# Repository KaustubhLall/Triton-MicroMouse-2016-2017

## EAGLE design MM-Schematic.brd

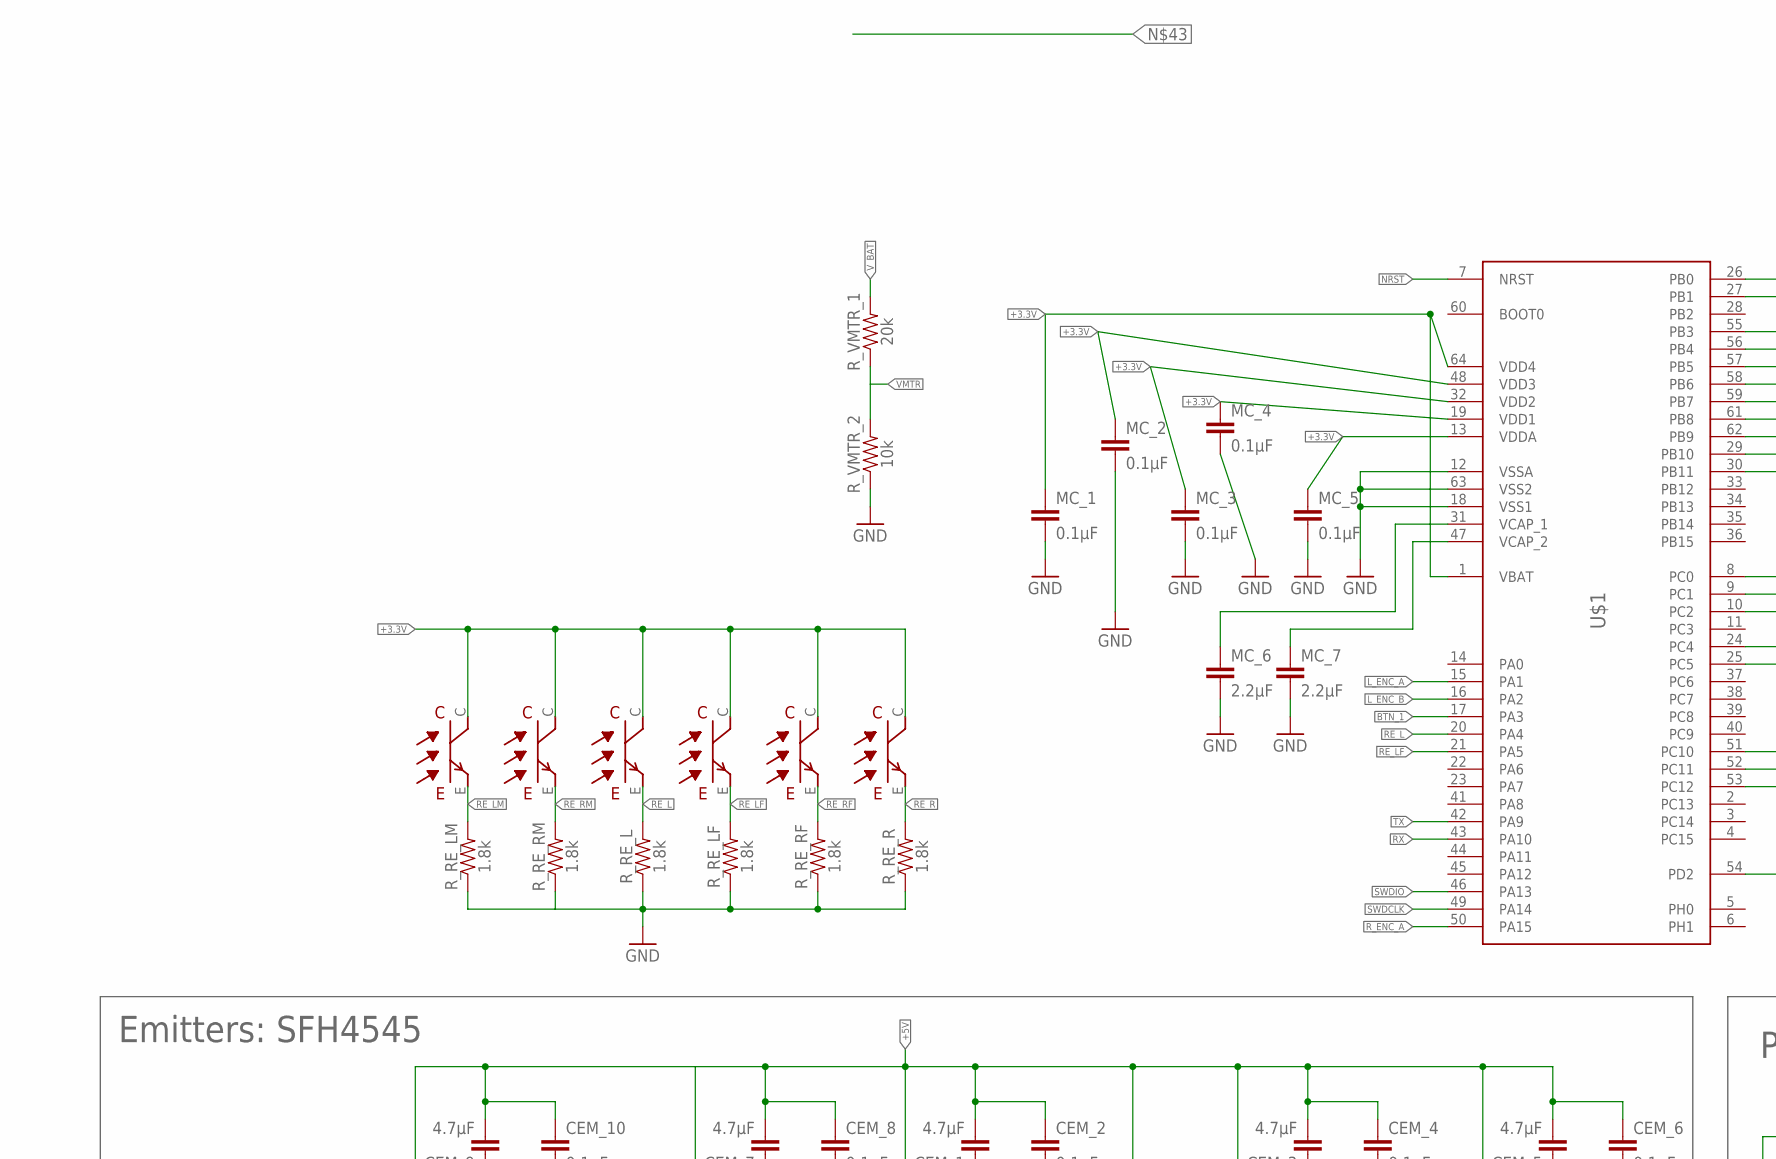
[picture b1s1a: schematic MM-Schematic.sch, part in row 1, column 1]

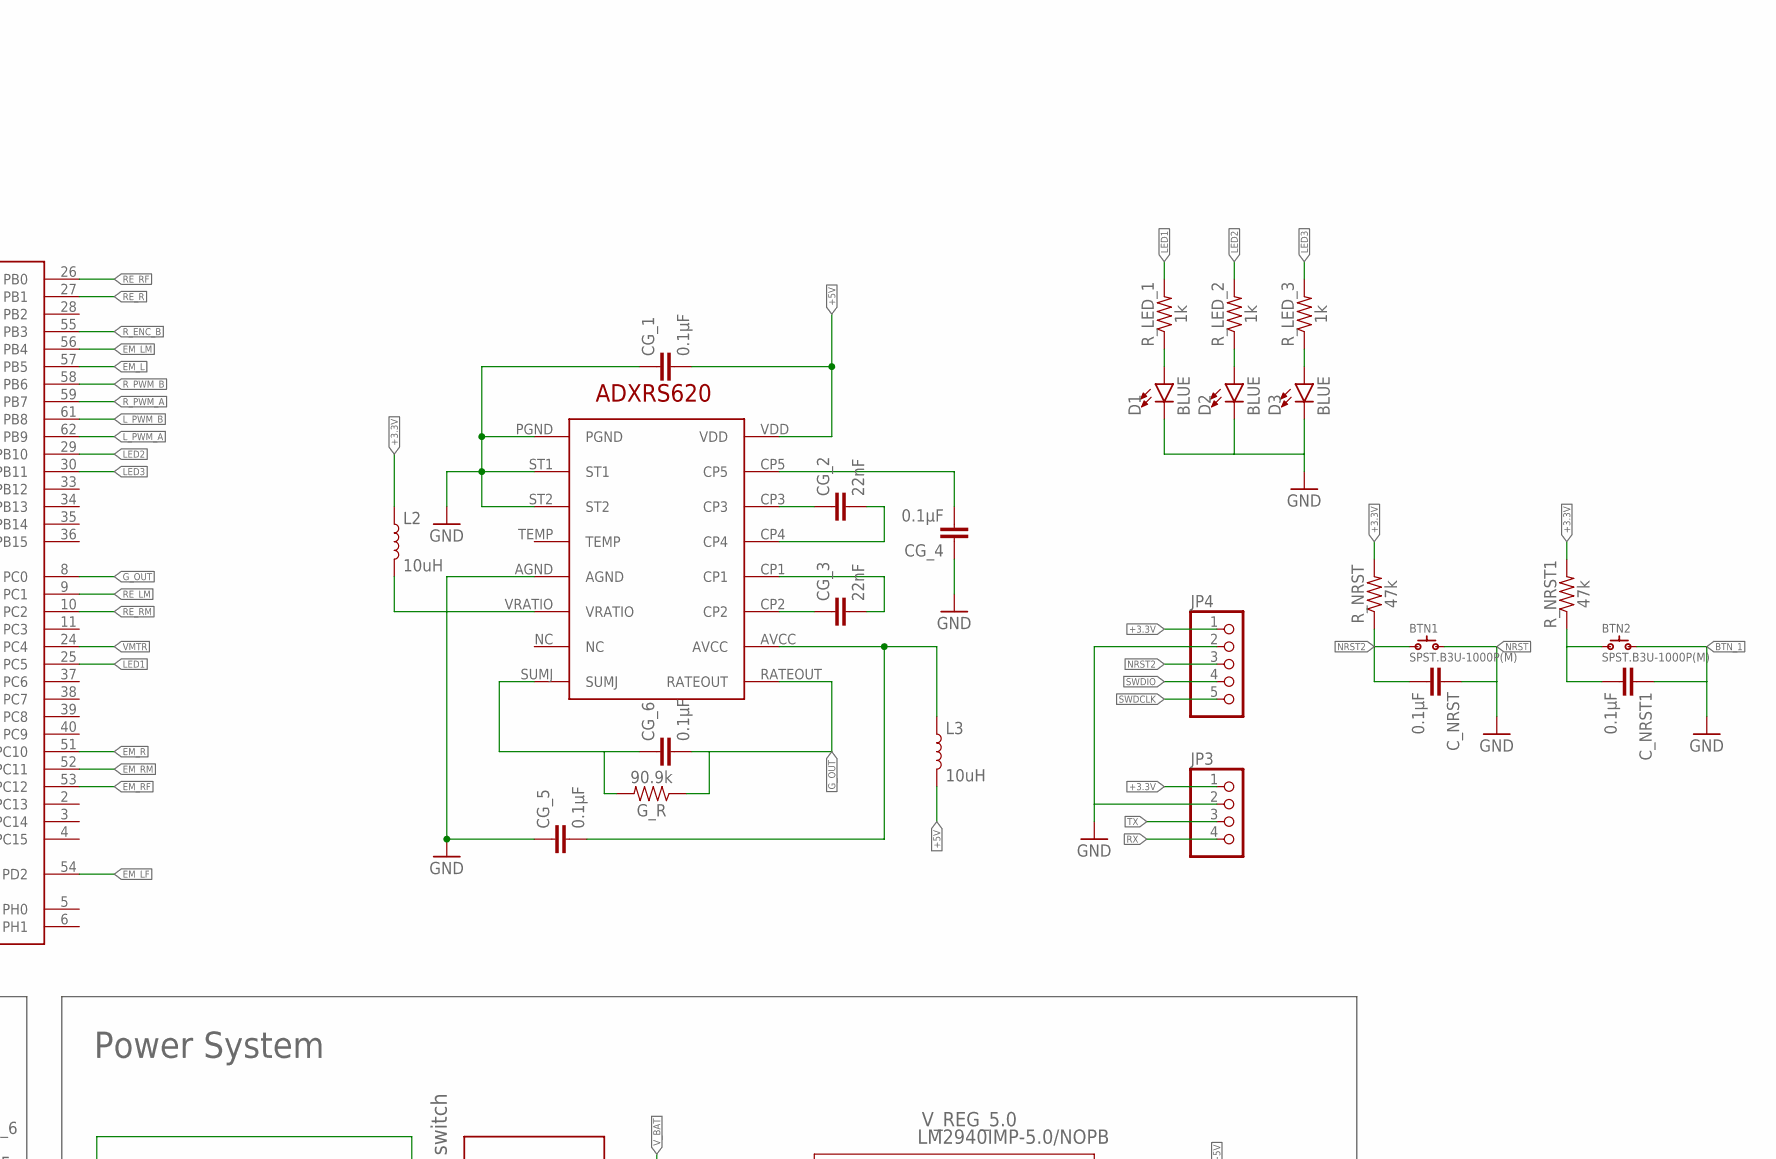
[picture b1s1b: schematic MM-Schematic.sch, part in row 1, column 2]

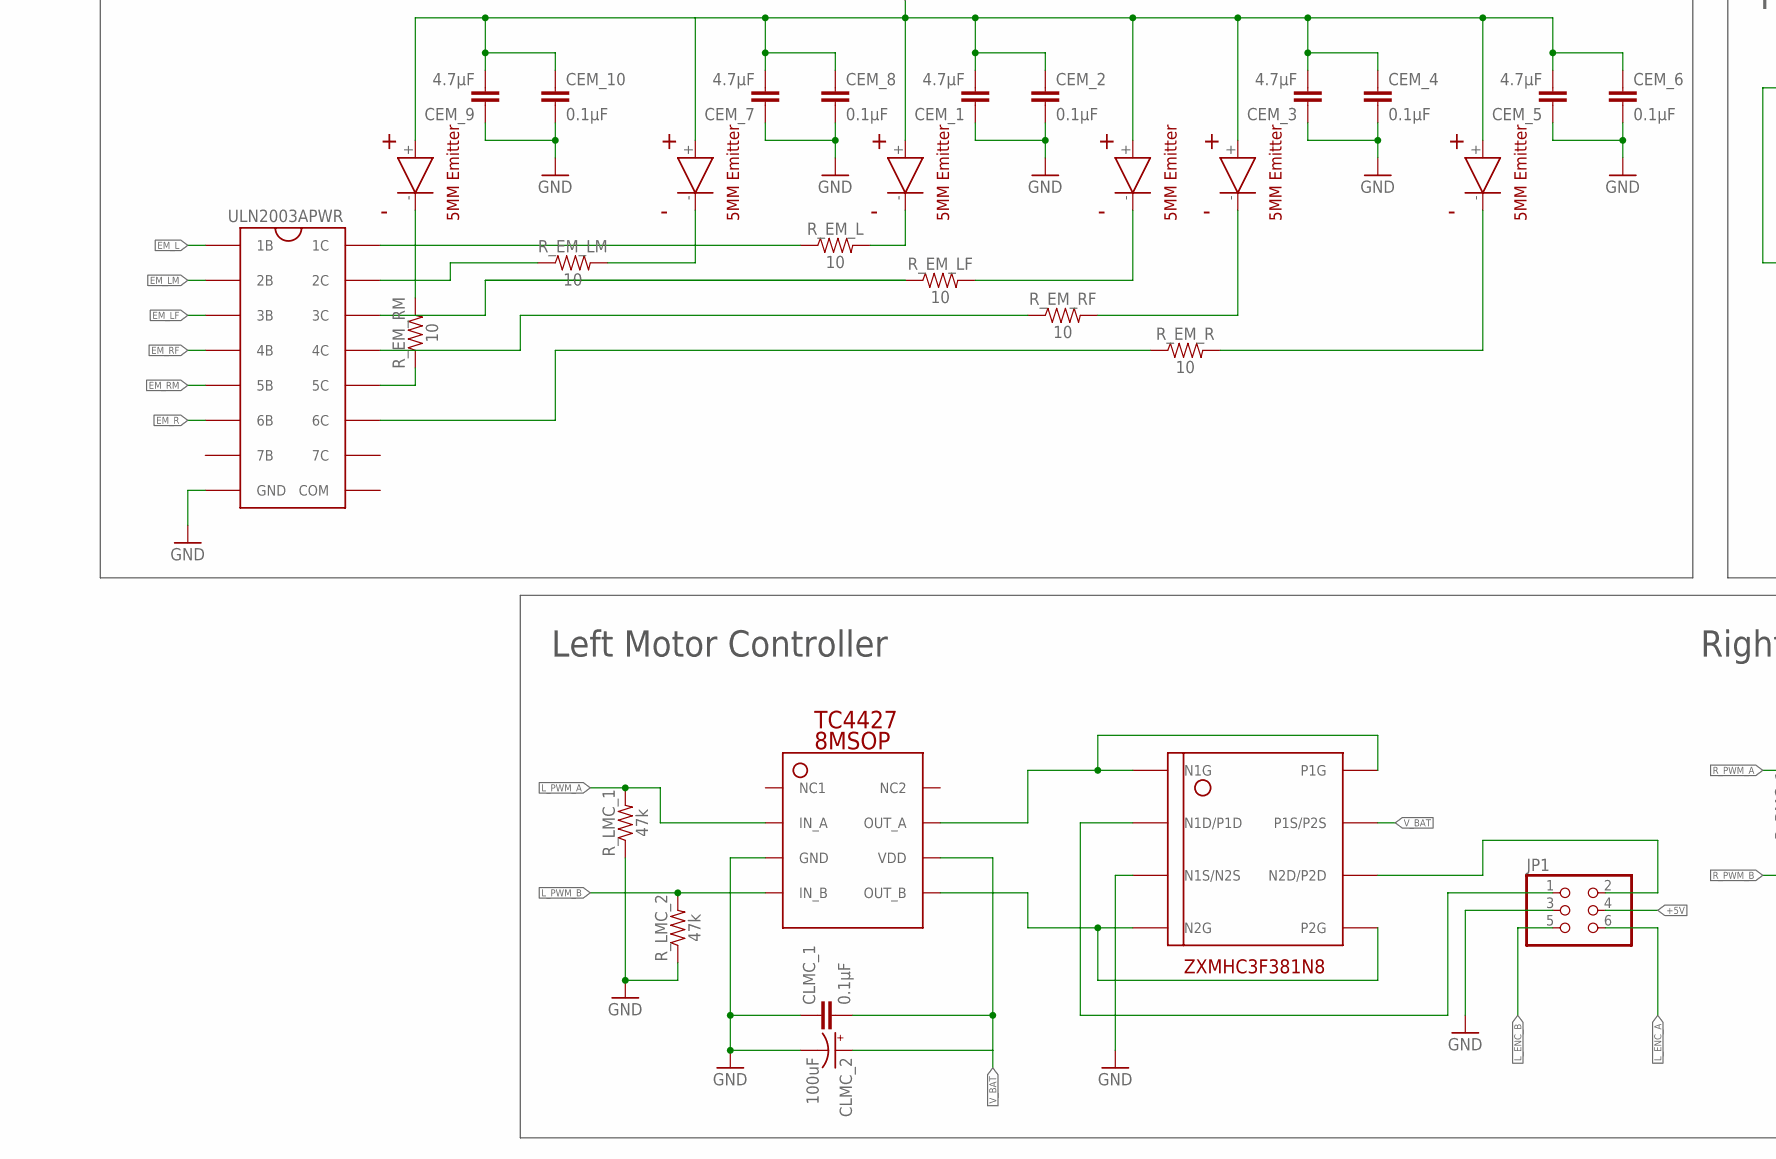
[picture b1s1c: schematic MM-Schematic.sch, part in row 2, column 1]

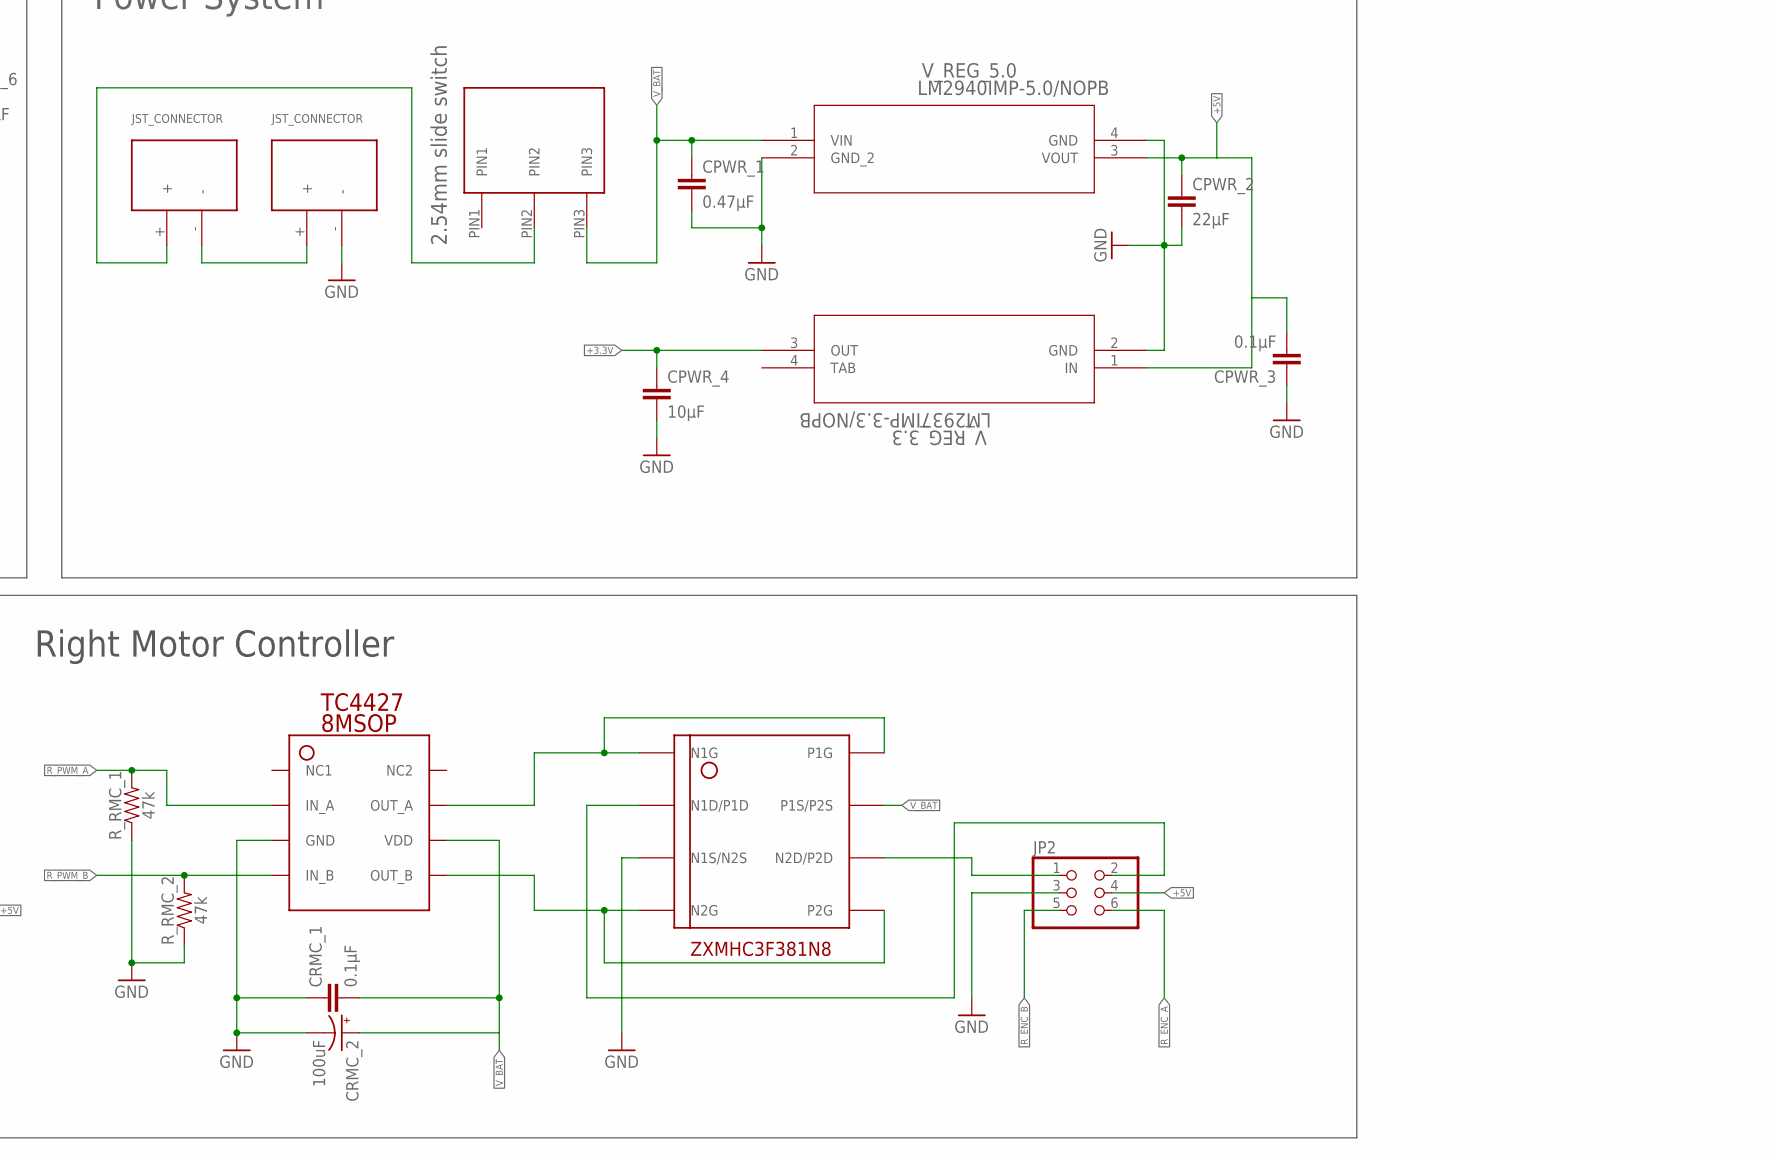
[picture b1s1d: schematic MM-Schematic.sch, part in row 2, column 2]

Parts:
BTN1, BTN2: SPST.B3U-1000P(M); B3U-1000P(M)
CEM_1, CEM_3, CEM_5, CEM_7, CEM_9: 4.7µF; 0805
CEM_2, CEM_4, CEM_6, CEM_8, CEM_10: 0.1µF; 0805
CG_1, CG_4, CG_5, CG_6: 0.1µF; 0805
CG_2, CG_3: 22nF; 0805
CLMC_1: 0.1µF; 0805
CLMC_2: 100uF; EIA7343
CPWR_1: 0.47µF; 0805
CPWR_2: 22µF; 0805
CPWR_3: 0.1µF; 0805
CPWR_4: 10µF; 0805
CRMC_1: 0.1µF; 0805
CRMC_2: 100uF; EIA7343
C_NRST, C_NRST1: 0.1µF; 0805
D1, D2, D3: BLUE; LED-0603
G_R: 90.9k; 0805
JP1, JP2: PINHD-2X3; 2X03
JP3: PINHD-1X4; 1X04
JP4: PINHD-1X55X2MM; 1_05X2MM
L2, L3: 10uH; 0805
MC_1, MC_2, MC_3, MC_4, MC_5: 0.1µF; 0805
MC_6, MC_7: 2.2µF; 0805
R_EM_L: 10; 0805
R_EM_LF: 10; 0805
R_EM_LM: 10; 0805
R_EM_R: 10; 0805
R_EM_RF: 10; 0805
R_EM_RM: 10; 0805
R_LED_1, R_LED_2, R_LED_3: 1k; 0805
R_LMC_1, R_LMC_2: 47k; 0805
R_NRST, R_NRST1: 47k; 0805
R_RE_L: 1.8k; 0805
R_RE_LF: 1.8k; 0805
R_RE_LM: 1.8k; 0805
R_RE_R: 1.8k; 0805
R_RE_RF: 1.8k; 0805
R_RE_RM: 1.8k; 0805
R_RMC_1, R_RMC_2: 47k; 0805
R_VMTR_1: 20k; 0805
R_VMTR_2: 10k; 0805
U$1: STM32F405XXSTM32F405XX; LQFP64
U$2, U$3, U$4, U$5, U$22, U$23: RECEIVER
U$6: ADXRS620
U$7, U$8, U$9, U$10, U$20, U$21: EMITTER
U$11: ULN2003APWR
U$12, U$13: JST_CONNECTOR_FEMALE
U$14: TS02_SWITCH
U$15, U$17: TC4427(8MSOP)
U$16, U$18: ZXMHC3F381N8
V_REG_3.3: LM2937IMP-3.3/NOPB; MP04A
V_REG_5.0: LM2940IMP-5.0/NOPB; MP04A

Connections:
+3.3V: CPWR_4.1, JP3.1, JP4.1, L2.1, MC_1.1, MC_2.1, MC_3.1, MC_4.1, MC_5.1, R_NRST.2, R_NRST1.2, U$1.1 (VBAT), U$1.13 (VDDA), U$1.19 (VDD1), U$1.32 (VDD2), U$1.48 (VDD3), U$1.64 (VDD4), U$2.C, U$3.C, U$4.C, U$5.C, U$22.C, U$23.C, V_REG_3.3.3 (OUT)
+5V: CEM_1.2, CEM_2.1, CEM_3.2, CEM_4.1, CEM_5.2, CEM_6.1, CEM_7.2, CEM_8.1, CEM_9.2, CEM_10.1, CG_1.2, CPWR_2.1, CPWR_3.2, JP1.4, JP2.4, L3.2, U$6.VDD, U$7.+, U$8.+, U$9.+, U$10.+, U$20.+, U$21.+, V_REG_3.3.1 (IN), V_REG_5.0.3 (VOUT)
BTN_1: BTN2.2, C_NRST1.1, U$1.17 (PA3)
EM_L: U$1.57 (PB5), U$11.1B
EM_LF: U$1.54 (PD2), U$11.3B
EM_LM: U$1.56 (PB4), U$11.2B
EM_R: U$1.51 (PC10), U$11.6B
EM_RF: U$1.53 (PC12), U$11.4B
EM_RM: U$1.52 (PC11), U$11.5B
GND: CEM_1.1, CEM_2.2, CEM_3.1, CEM_4.2, CEM_5.1, CEM_6.2, CEM_7.1, CEM_8.2, CEM_9.1, CEM_10.2, CG_4.1, CG_5.1, CLMC_1.1, CLMC_2.C (-), CPWR_1.2, CPWR_2.2, CPWR_3.1, CPWR_4.2, CRMC_1.1, CRMC_2.C (-), D1.C, D2.C, D3.C, JP1.3, JP2.3, JP3.2, JP4.2, MC_1.2, MC_2.2, MC_3.2, MC_4.2, MC_5.2, MC_6.2, MC_7.2, R_LMC_1.1, R_LMC_2.1, R_RE_L.1, R_RE_LF.1, R_RE_LM.1, R_RE_R.1, R_RE_RF.1, R_RE_RM.1, R_RMC_1.1, R_RMC_2.1, R_VMTR_2.1, U$1.12 (VSSA), U$1.18 (VSS1), U$1.63 (VSS2), U$6.AGND, U$11.GND, U$13.-, U$15.GND, U$16.N1S/N2S, U$17.GND, U$18.N1S/N2S, V_REG_3.3.2 (GND), V_REG_5.0.2 (GND_2), V_REG_5.0.4 (GND)
G_OUT: CG_6.2, G_R.1, U$1.8 (PC0), U$6.RATEOUT
LED1: R_LED_1.2, U$1.25 (PC5)
LED2: R_LED_2.2, U$1.29 (PB10)
LED3: R_LED_3.2, U$1.30 (PB11)
L_ENC_A: JP1.6, U$1.15 (PA1)
L_ENC_B: JP1.5, U$1.16 (PA2)
L_PWM_A: R_LMC_1.2, U$1.62 (PB9), U$15.IN_A
L_PWM_B: R_LMC_2.2, U$1.61 (PB8), U$15.IN_B
unnamed: CG_5.2, L3.1, U$6.AVCC
unnamed: D2.A, R_LED_2.1
unnamed: CG_1.1, U$6.PGND, U$6.ST1, U$6.ST2
unnamed: CG_4.2, U$6.CP5
unnamed: CG_2.2, U$6.CP4
unnamed: MC_6.1, U$1.31 (VCAP_1)
unnamed: MC_7.1, U$1.47 (VCAP_2)
unnamed: CG_2.1, U$6.CP3
unnamed: CG_3.1, U$6.CP2
unnamed: CG_3.2, U$6.CP1
unnamed: L2.2, U$6.VRATIO
unnamed: CG_6.1, G_R.2, U$6.SUMJ
unnamed: U$12.-, U$13.+
unnamed: U$12.+, U$14.PIN2
unnamed: R_EM_L.2, U$7.-
unnamed: R_EM_L.1, U$11.1C
unnamed: R_EM_LF.1, U$11.3C
unnamed: D1.A, R_LED_1.1
unnamed: R_EM_RF.1, U$11.4C
unnamed: R_EM_RF.2, U$9.-
unnamed: R_EM_R.1, U$11.6C
unnamed: R_EM_R.2, U$10.-
unnamed: U$15.OUT_B, U$16.N2G, U$16.P2G
unnamed: U$15.OUT_A, U$16.N1G, U$16.P1G
unnamed: JP1.1, U$16.N1D/P1D
unnamed: JP1.2, U$16.N2D/P2D
unnamed: U$17.OUT_B, U$18.N2G, U$18.P2G
unnamed: U$17.OUT_A, U$18.N1G, U$18.P1G
unnamed: JP2.2, U$18.N1D/P1D
unnamed: JP2.1, U$18.N2D/P2D
unnamed: D3.A, R_LED_3.1
unnamed: BTN2.1, C_NRST1.2, R_NRST1.1
unnamed: R_EM_LM.1, U$11.2C
unnamed: R_EM_LM.2, U$20.-
unnamed: R_EM_RM.2, U$21.-
unnamed: R_EM_RM.1, U$11.5C
NRST: BTN1.2, C_NRST.1, U$1.7 (NRST)
NRST2: BTN1.1, C_NRST.2, JP4.3, R_NRST.1
RE_L: R_RE_L.2, U$1.20 (PA4), U$2.E
RE_LF: R_RE_LF.2, U$1.21 (PA5), U$3.E
RE_LM: R_RE_LM.2, U$1.9 (PC1), U$23.E
RE_R: R_RE_R.2, U$1.27 (PB1), U$5.E
RE_RF: R_RE_RF.2, U$1.26 (PB0), U$4.E
RE_RM: R_RE_RM.2, U$1.10 (PC2), U$22.E
RX: JP3.4, U$1.43 (PA10)
R_EM_RF: R_EM_LF.2, U$8.-
R_ENC_A: JP2.6, U$1.50 (PA15)
R_ENC_B: JP2.5, U$1.55 (PB3)
R_PWM_A: R_RMC_1.2, U$1.59 (PB7), U$17.IN_A
R_PWM_B: R_RMC_2.2, U$1.58 (PB6), U$17.IN_B
SWDCLK: JP4.5, U$1.49 (PA14)
SWDIO: JP4.4, U$1.46 (PA13)
TAB: V_REG_3.3.4 (TAB)
TX: JP3.3, U$1.42 (PA9)
VMTR: R_VMTR_1.1, R_VMTR_2.2, U$1.24 (PC4)
V_BAT: CLMC_1.2, CLMC_2.A (+), CPWR_1.1, CRMC_1.2, CRMC_2.A (+), R_VMTR_1.2, U$14.PIN3, U$15.VDD, U$16.P1S/P2S, U$17.VDD, U$18.P1S/P2S, V_REG_5.0.1 (VIN)

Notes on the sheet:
Emitters: SFH4545
Power System
Left Motor Controller
Right Motor Controller

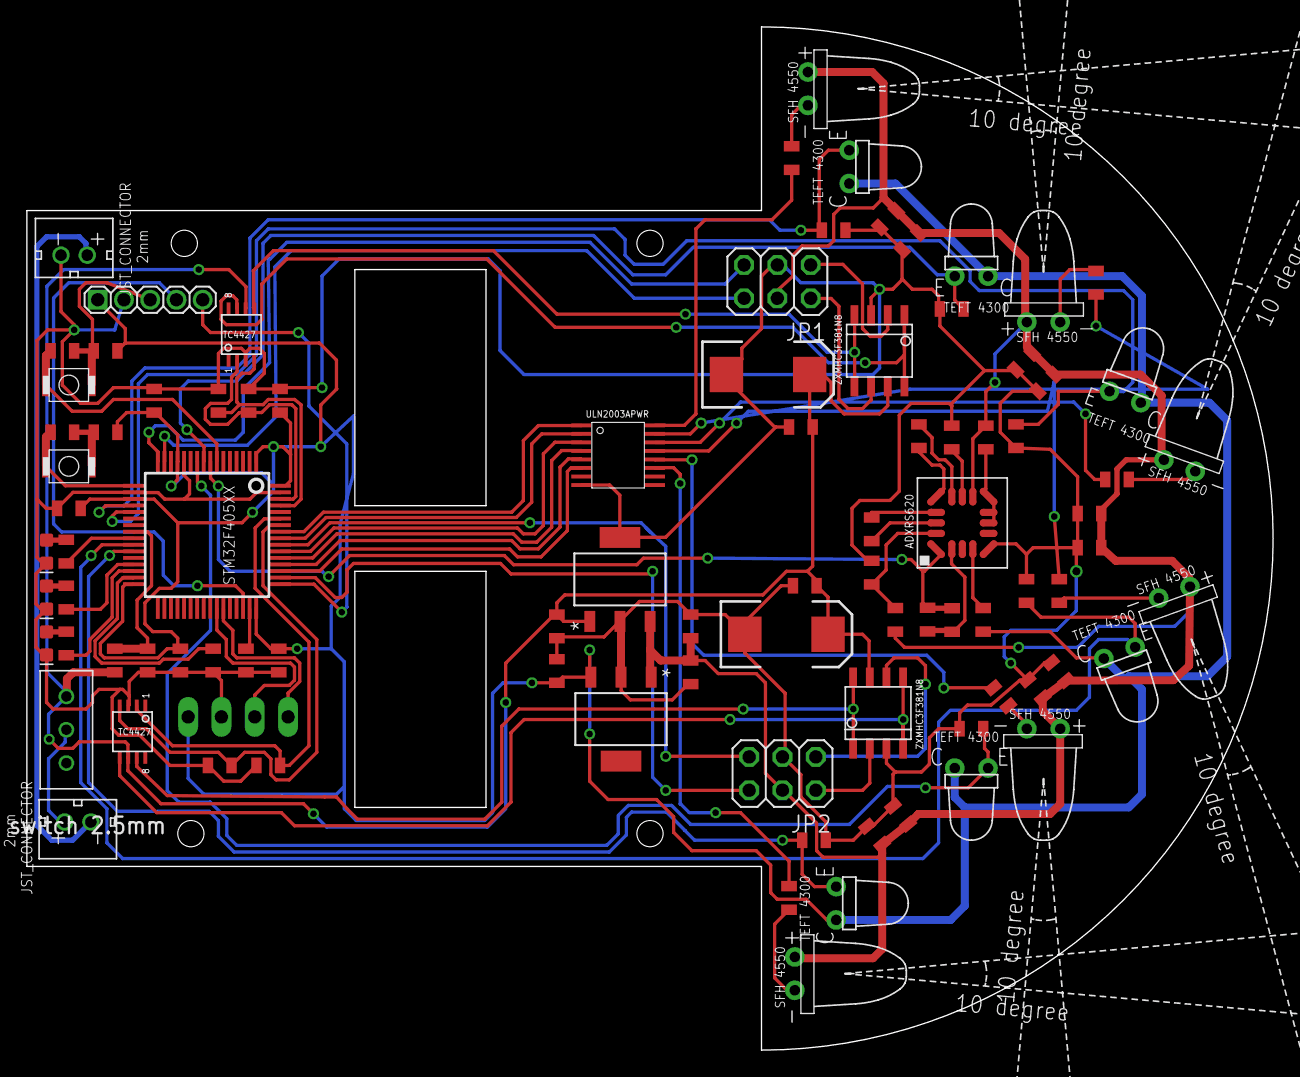
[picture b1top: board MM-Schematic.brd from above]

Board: 2 copper layers, 95.0 x 78.0 mm, 93 parts (1 on the bottom side), 73 nets.

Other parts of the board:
U$19: MOUSE10

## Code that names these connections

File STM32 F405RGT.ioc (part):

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Mcu.Name=STM32F405RGTx
Mcu.Package=LQFP64
Mcu.UserName=STM32F405RGTx
PA0-WKUP.Signal=GPIO_Output
PA1.GPIOParameters=GPIO_Label
PA1.GPIO_Label=L_ENC_A
PA1.Signal=S_TIM5_CH2
PA10.Mode=Asynchronous
PA10.Signal=USART1_RX
PA15.GPIOParameters=GPIO_Label
PA15.GPIO_Label=R_ENC_A
PA15.Signal=S_TIM2_CH1_ETR
PA2.GPIOParameters=GPIO_Label
PA2.GPIO_Label=L_ENC_B
PA2.Signal=S_TIM5_CH3
PA3.GPIOParameters=GPIO_Label
PA3.GPIO_Label=Buttom_1
PA3.Signal=GPIO_Input
PA4.GPIOParameters=GPIO_Label
PA4.GPIO_Label=RE_L
PA4.Signal=ADCx_IN4
PA5.GPIOParameters=GPIO_Label
PA5.GPIO_Label=RE_LF
PA5.Signal=ADCx_IN5
PA9.Mode=Asynchronous
PA9.Signal=USART1_TX
PB0.GPIOParameters=GPIO_Label
PB0.GPIO_Label=RE_RF
PB0.Signal=ADCx_IN8
PB1.GPIOParameters=GPIO_Label
PB1.GPIO_Label=RE_R
PB1.Signal=ADCx_IN9
PB10.GPIOParameters=GPIO_Label
PB10.GPIO_Label=LED2
PB10.Signal=GPIO_Output
PB11.GPIOParameters=GPIO_Label
PB11.GPIO_Label=LED3
PB11.Signal=GPIO_Output
PB3.GPIOParameters=GPIO_Label
PB3.GPIO_Label=R_ENC_B
PB3.Signal=S_TIM2_CH2
PB4.GPIOParameters=GPIO_Label
PB4.GPIO_Label=EM_LM
PB4.Signal=GPIO_Output
PB5.GPIOParameters=GPIO_Label
PB5.GPIO_Label=EM_L
PB5.Signal=GPIO_Output
PB6.GPIOParameters=GPIO_Label
PB6.GPIO_Label=R_PWM_B
PB6.Signal=S_TIM4_CH1
PB7.GPIOParameters=GPIO_Label
PB7.GPIO_Label=R_PWM_A
PB7.Signal=S_TIM4_CH2
PB8.GPIOParameters=GPIO_Label
PB8.GPIO_Label=L_PWM_B
PB8.Signal=S_TIM4_CH3
PB9.GPIOParameters=GPIO_Label
PB9.GPIO_Label=L_PWM_A
PB9.Signal=S_TIM4_CH4
PC1.GPIOParameters=GPIO_Label
PC1.GPIO_Label=RE_LM
PC1.Signal=ADCx_IN11
PC10.GPIOParameters=GPIO_Label
PC10.GPIO_Label=EM_R
PC10.Signal=GPIO_Output
PC11.GPIOParameters=GPIO_Label
PC11.GPIO_Label=EM_RM
PC11.Signal=GPIO_Output
PC12.GPIOParameters=GPIO_Label
PC12.GPIO_Label=EM_RF
PC12.Signal=GPIO_Output
PC2.GPIOParameters=GPIO_Label
PC2.GPIO_Label=RE_RM
PC2.Signal=ADCx_IN12
PC4.GPIOParameters=GPIO_Label
PC4.GPIO_Label=VMTR
PC4.Signal=GPIO_Analog
PC5.GPIOParameters=GPIO_Label
PC5.GPIO_Label=LED1
PC5.Signal=GPIO_Output
PC6.Signal=S_TIM3_CH1
PC7.Signal=S_TIM3_CH2
PD2.GPIOParameters=GPIO_Label
PD2.GPIO_Label=EM_LF
PD2.Signal=GPIO_Output
RCC.HSE_VALUE=25000000
RCC.SYSCLKFreq_VALUE=16000000

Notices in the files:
parts and their libraries:
SparkFun-Capacitors: Licensing: Creative Commons ShareAlike 4.0 International - https://creativecommons.org/licenses/by-sa/4.0
COPYRIGHT: Copyright C 2015 Accelerated Designs. All rights reserved
